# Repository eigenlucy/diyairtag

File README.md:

# diyairtag

Wooohooo a new package!

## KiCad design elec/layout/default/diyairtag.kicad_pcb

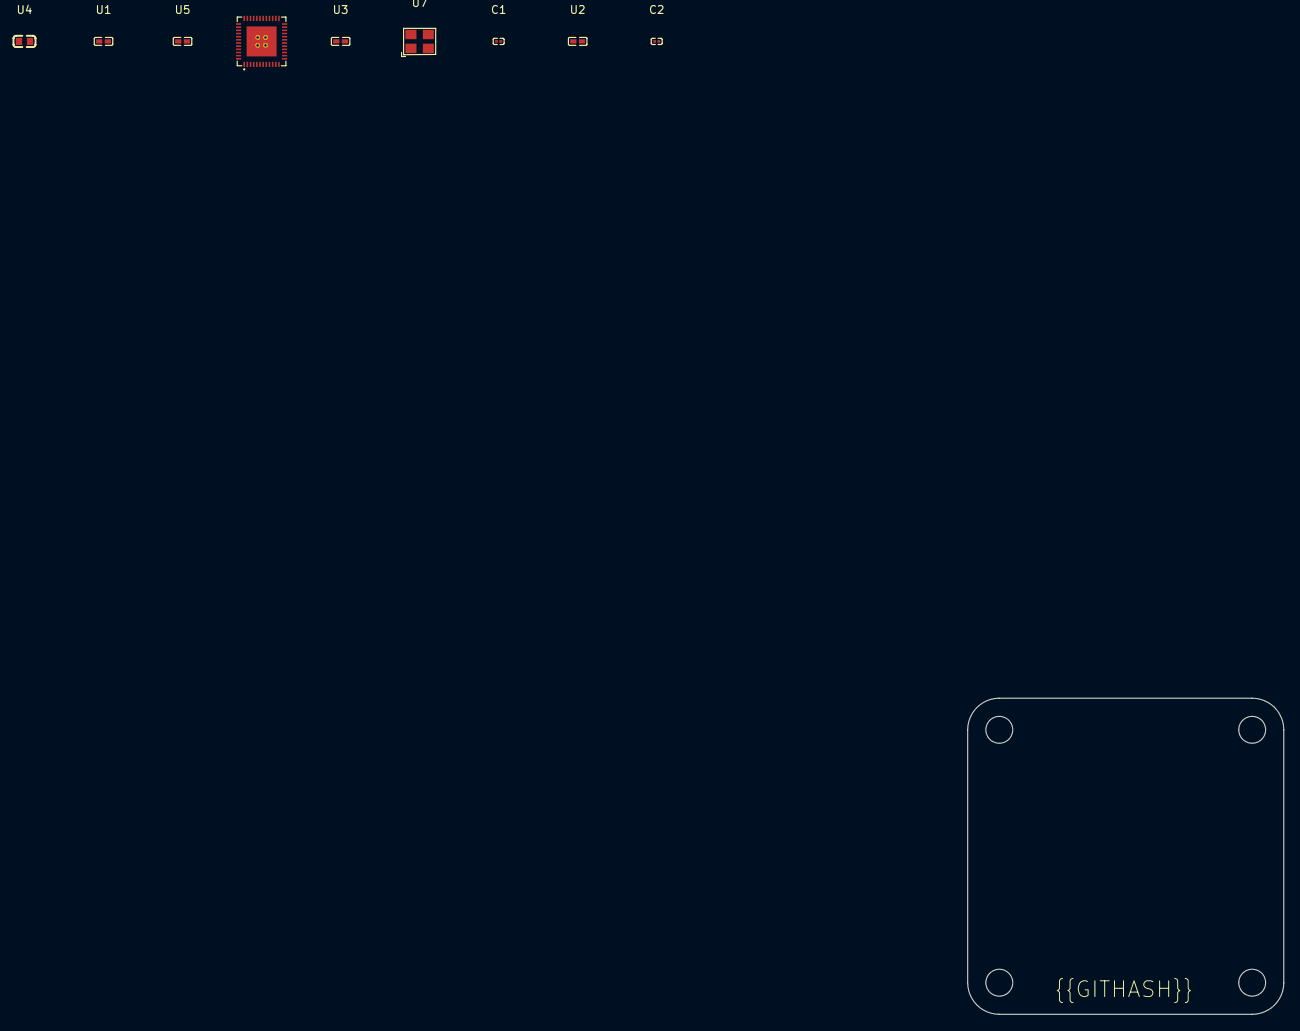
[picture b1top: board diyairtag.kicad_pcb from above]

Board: 2 copper layers, 40.0 x 40.0 mm, 9 parts (0 on the bottom side), 6 nets, no tracks yet.

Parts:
C1, C2: C0201-a4ec75
U1: 1nF ±10% 50V X7R; C0402-b3ef17
U2, U5: 100nF ±10% 16V X7R; C0402-b3ef17
U3: 47nF ±10% 50V X7R; C0402-b3ef17
U4: 4.7µF ±10% 10V X5R; C0603-bd72f6
U6: QFN-48_L6.0-W6.0-P0.40-BL-EP3.8
U7: OSC-SMD_4P-L3.2-W2.5-BL

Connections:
DEC1: U2.1, U6.39
DEC2: U3.1, U6.29
gnd: C1.2, C2.2, U1.2, U2.2, U3.2, U4.2, U5.2, U6.13, U6.33, U6.34, U7.2, U7.4
hv: U1.1, U4.1, U5.1, U6.1, U6.12, U6.35, U6.36
xin: C1.1, U6.37, U7.3
xout: C2.1, U6.38, U7.1

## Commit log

2025-02-02 Configure project
2025-02-04 initial nrf build
2025-02-04 failed build
2025-02-04 esoteric api error
2025-02-05 esoteric api errors THE RETURN
2025-02-06 esoteric pick errors
2025-02-08 fixed adjacent
